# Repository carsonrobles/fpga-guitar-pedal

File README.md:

# FPGA Multi-Effect Guitar Pedal
Carson Robles

## Project Description
This project strives to implement a multi-effect guitar pedal using an FPGA for all of the signal processing.

### Status
In development.

### Goal
The goal of this project is to take the place of multiple separate traditional guitar pedals each with its own dedicated effect.

## Effects
Below is a list of the currently working effects followed by a list of effects that are in development or are planned for future development.

### Working Effects
- Delay
- Distortion (variable gain hard clipping)
- Flanger
- Tremolo

### Effects in Development or Planned for the Future
- Wah Wah
- Phaser

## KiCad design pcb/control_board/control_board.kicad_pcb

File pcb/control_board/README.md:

# FPGA Multi-Effect Guitar Pedal
Carson Robles

## Control Board
The main function of this board is to hold all components of the project including: the FPGA board, the data converter module, control knobs, foot switches, and enable LEDs.

### Status
In fabrication.

## Board Images
### Power System Schematic

Schematic of the power supply that the system runs on. The board accepts 12V in through the onboard barrel jack and produces a regulated 5V supply to power the entire system.

### Effect Enables and Settings Schematic

Schematic of the effect enables and settings potentiometers. These include the 5 foot switches used to enable and disable individual effects. Each effect also includes 2 potentiometer knobs that allow the user to modify each effect to their liking.

### FPGA Board Connections and Analog Mux Schematic

The FPGA is mounted onto the control board via 2 24 pin headers. The analog mux allows only one potentiometer voltage to pass at a time that the FPGA can read using its onboard ADC. The FPGA cycles through which potentiometer value it reads and updates its saved values when a new value is read. The output of the analog mux is filtered and divided down to the range that the onboard ADC can handle, 3.3V.

### Data Converter Module Connections

The data converter module is also mounted to the control board via a Digilent PMOD header (2x6 pin header). This header is routed to I/O pins on the FPGA.

### Front of Board Layout

### Back of Board Layout

### Front of Board Rendering

### Back of Board Rendering

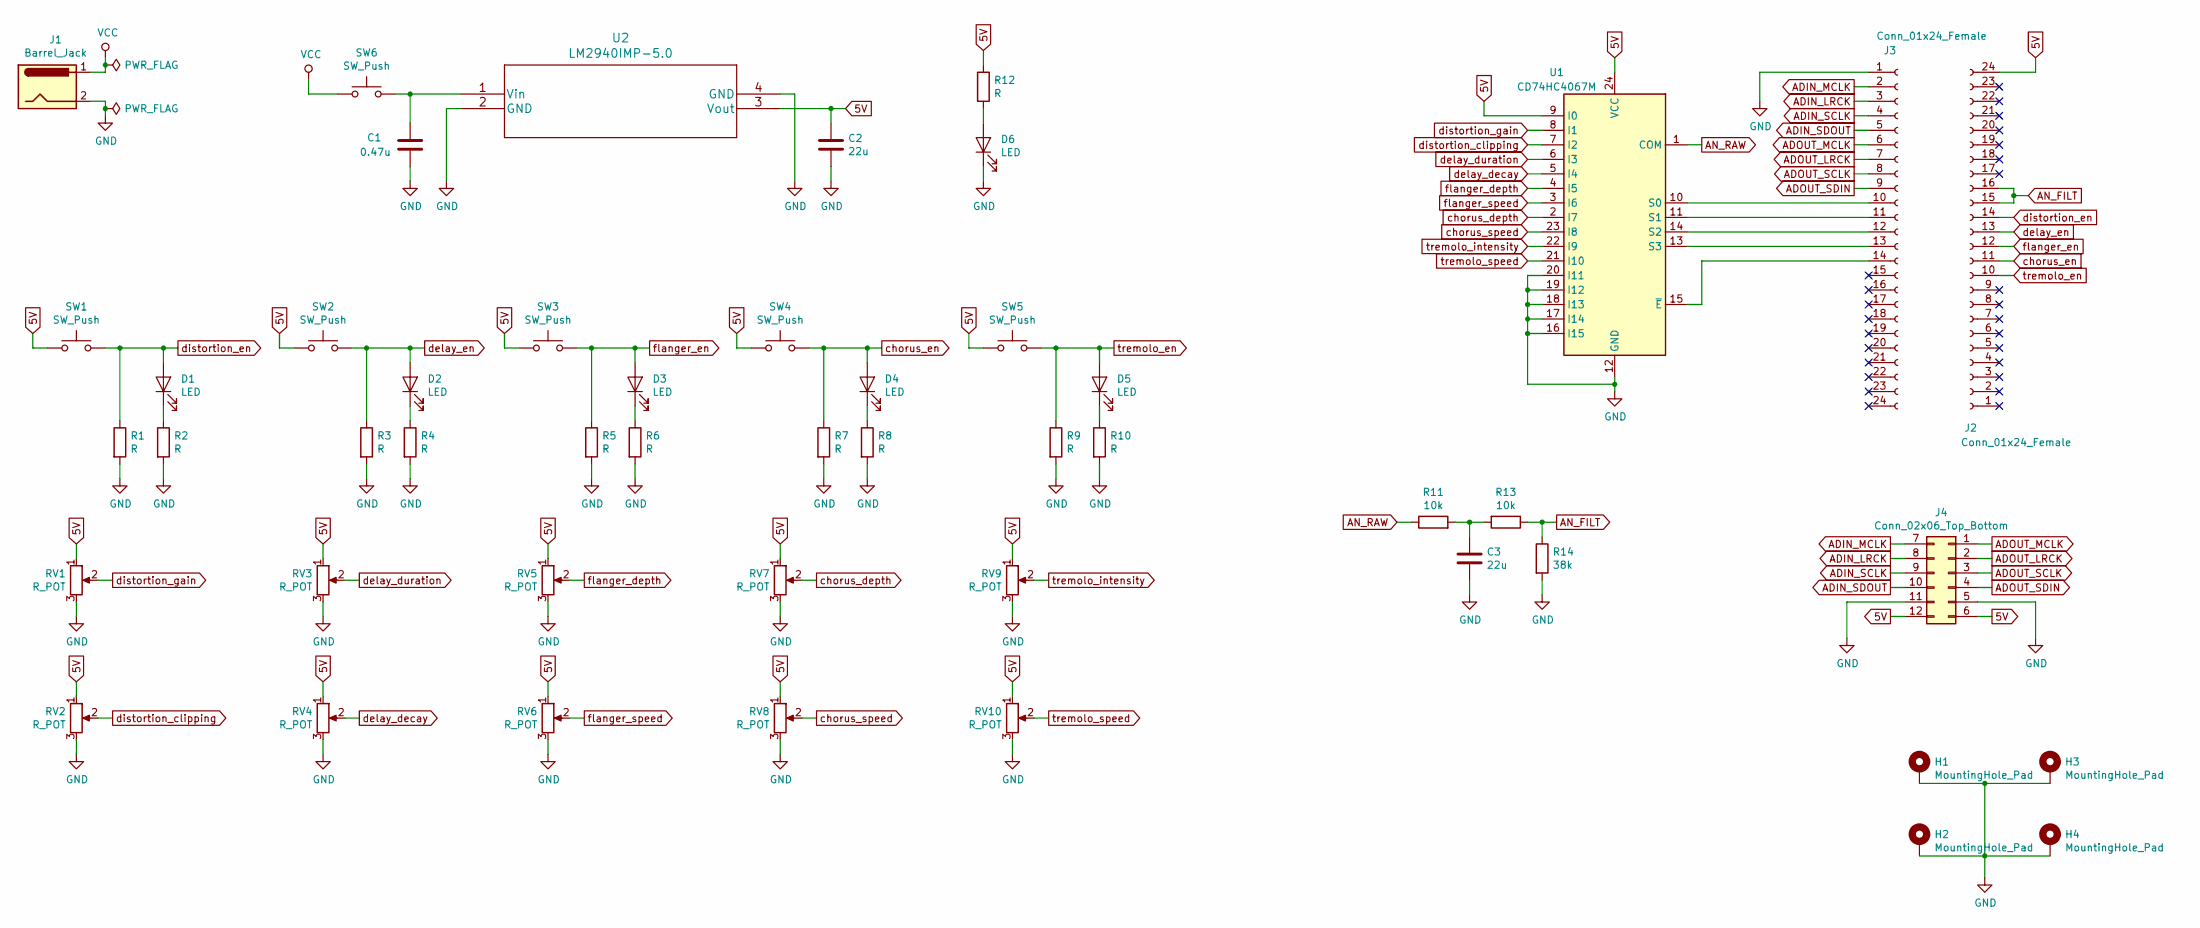
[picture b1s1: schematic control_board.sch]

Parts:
C1: 0.47u; C_0805_2012Metric_Pad1.15x1.40mm_HandSolder
C2, C3: 22u; C_0805_2012Metric_Pad1.15x1.40mm_HandSolder
D1, D2, D3, D4, D5, D6: LED; LED_D4.0mm
H1, H2, H3, H4: MountingHole_Pad; MountingHole_2.5mm_Pad
J1: Barrel_Jack; BarrelJack_CUI_PJ-102AH_Horizontal
J2, J3: Conn_01x24_Female; PinSocket_1x24_P2.54mm_Vertical
J4: Conn_02x06_Top_Bottom; PinHeader_2x06_P2.54mm_Vertical
R1, R2, R3, R4, R5, R6, R7, R8, R9, R10, R12: R; R_0805_2012Metric_Pad1.15x1.40mm_HandSolder
R11, R13: 10k; R_0805_2012Metric_Pad1.15x1.40mm_HandSolder
R14: 38k; R_0805_2012Metric_Pad1.15x1.40mm_HandSolder
RV1, RV2, RV3, RV4, RV5, RV6, RV7, RV8, RV9, RV10: R_POT; Potentiometer_Omeg_PC16BU_Vertical
SW1, SW2, SW3, SW4, SW5, SW6: SW_Push; PinHeader_2x01_P2.54mm_Vertical
U1: CD74HC4067M; SOIC-24W_7.5x15.4mm_P1.27mm
U2: LM2940IMP-5.0

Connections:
5V: C2.1, J2.24, J4.6, J4.12, R12.1, RV1.1, RV2.1, RV3.1, RV4.1, RV5.1, RV6.1, RV7.1, RV8.1, RV9.1, RV10.1, SW1.1, SW2.1, SW3.1, SW4.1, SW5.1, U1.9 (I0), U1.24 (VCC), U2.3 (Vout)
ADIN_LRCK: J3.3, J4.8
ADIN_MCLK: J3.2, J4.7
ADIN_SCLK: J3.4, J4.9
ADIN_SDOUT: J3.5, J4.10
ADOUT_LRCK: J3.7, J4.2
ADOUT_MCLK: J3.6, J4.1
ADOUT_SCLK: J3.8, J4.3
ADOUT_SDIN: J3.9, J4.4
AN_FILT: J2.15, J2.16, R13.1, R14.1
AN_RAW: R11.1, U1.1 (COM)
GND: C1.2, C2.2, C3.2, D6.1 (K), H1.1, H2.1, H3.1, H4.1, J1.2, J3.1, J4.5, J4.11, R1.2, R2.2, R3.2, R4.2, R5.2, R6.2, R7.2, R8.2, R9.2, R10.2, R14.2, RV1.3, RV2.3, RV3.3, RV4.3, RV5.3, RV6.3, RV7.3, RV8.3, RV9.3, RV10.3, U1.12 (GND), U1.16 (I15), U1.17 (I14), U1.18 (I13), U1.19 (I12), U1.20 (I11), U2.2 (GND), U2.4 (GND)
unnamed: C1.1, SW6.2, U2.1 (Vin)
unnamed: C3.1, R11.2, R13.2
unnamed: D1.1 (K), R2.1
unnamed: D2.1 (K), R4.1
unnamed: D3.1 (K), R6.1
unnamed: D4.1 (K), R8.1
unnamed: D5.1 (K), R10.1
unnamed: D6.2 (A), R12.2
unnamed: J3.10, U1.10 (S0)
unnamed: J3.11, U1.11 (S1)
unnamed: J3.12, U1.14 (S2)
unnamed: J3.13, U1.13 (S3)
unnamed: J3.14, U1.15 (~E)
VCC: J1.1, SW6.1
chorus_depth: RV7.2, U1.2 (I7)
chorus_en: D4.2 (A), J2.11, R7.1, SW4.2
chorus_speed: RV8.2, U1.23 (I8)
delay_decay: RV4.2, U1.5 (I4)
delay_duration: RV3.2, U1.6 (I3)
delay_en: D2.2 (A), J2.13, R3.1, SW2.2
distortion_clipping: RV2.2, U1.7 (I2)
distortion_en: D1.2 (A), J2.14, R1.1, SW1.2
distortion_gain: RV1.2, U1.8 (I1)
flanger_depth: RV5.2, U1.4 (I5)
flanger_en: D3.2 (A), J2.12, R5.1, SW3.2
flanger_speed: RV6.2, U1.3 (I6)
tremolo_en: D5.2 (A), J2.10, R9.1, SW5.2
tremolo_intensity: RV9.2, U1.22 (I9)
tremolo_speed: RV10.2, U1.21 (I10)

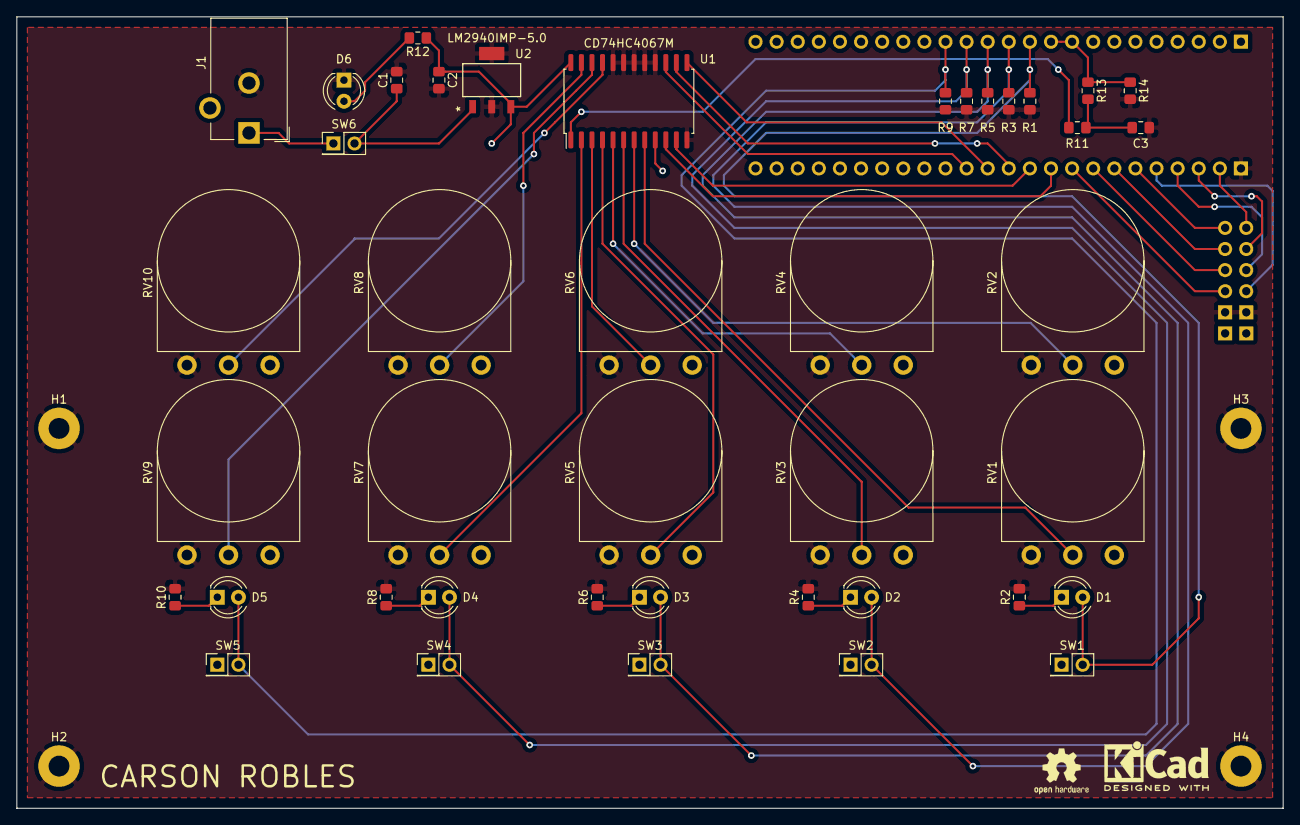
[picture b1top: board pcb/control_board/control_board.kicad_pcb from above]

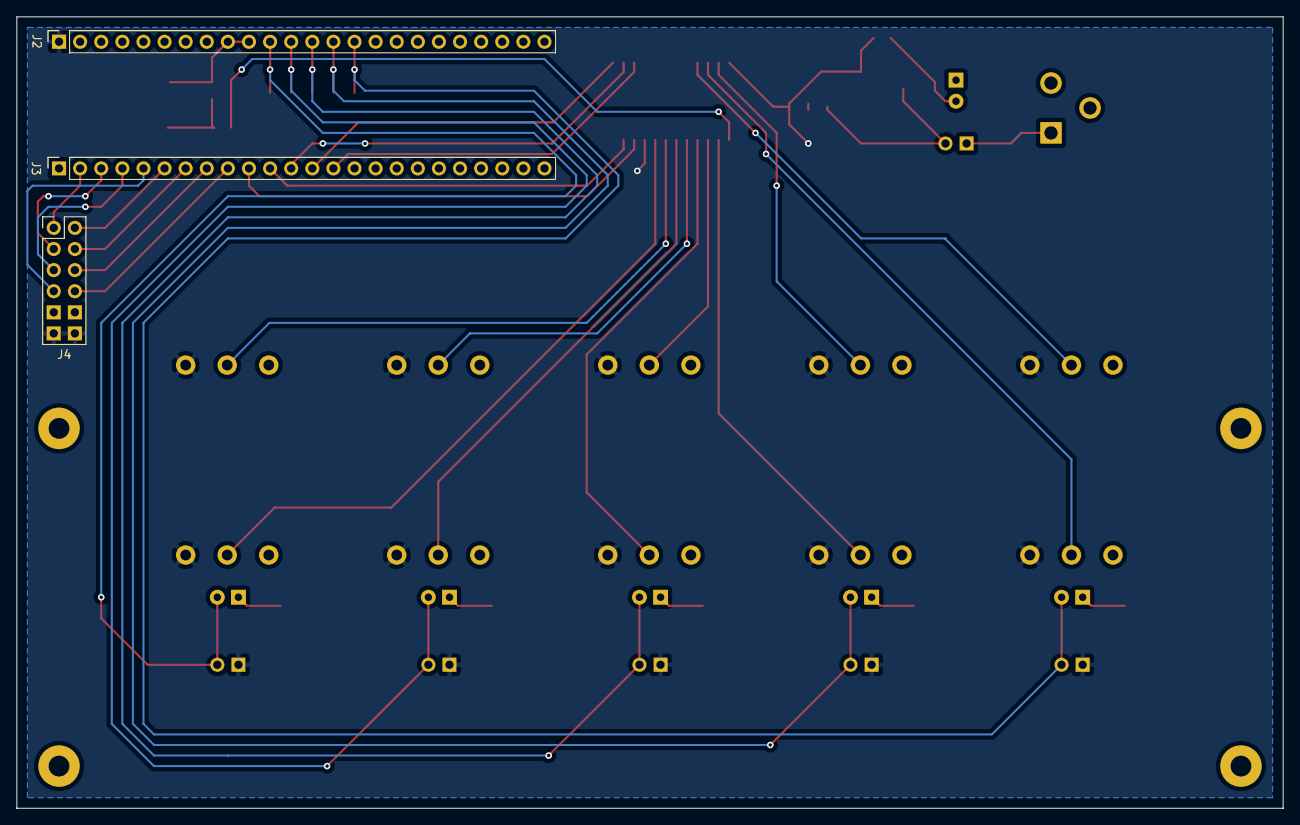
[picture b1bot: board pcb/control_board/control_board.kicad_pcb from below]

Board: 2 copper layers, 152.4 x 95.2 mm, 49 parts (3 on the bottom side), 41 nets.

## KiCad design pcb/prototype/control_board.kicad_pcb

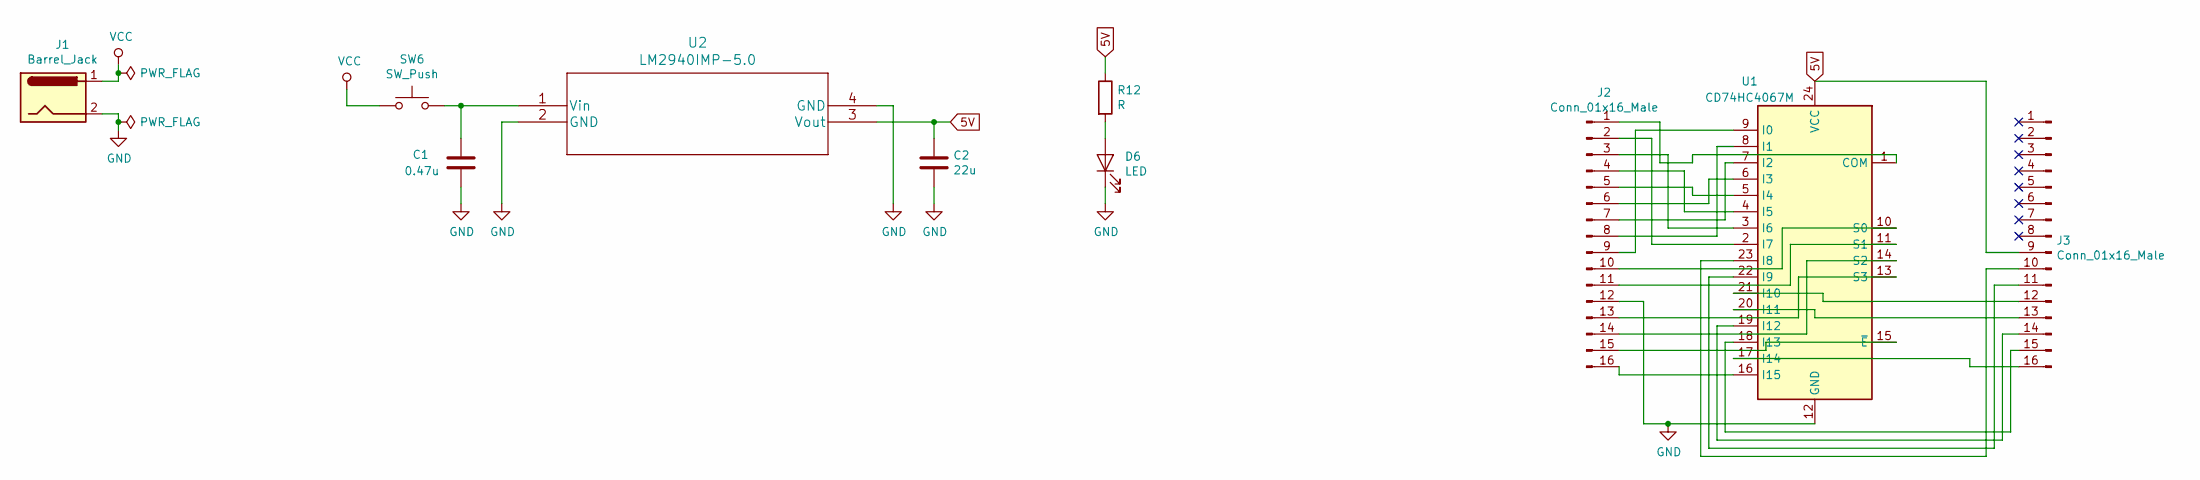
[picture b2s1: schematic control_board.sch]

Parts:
C1: 0.47u; C_0805_2012Metric_Pad1.15x1.40mm_HandSolder
C2: 22u; C_0805_2012Metric_Pad1.15x1.40mm_HandSolder
D6: LED; LED_D4.0mm
J1: Barrel_Jack; BarrelJack_CUI_PJ-102AH_Horizontal
J2, J3: Conn_01x16_Male; PinHeader_1x16_P2.54mm_Vertical
R12: R; R_Axial_DIN0309_L9.0mm_D3.2mm_P12.70mm_Horizontal
SW6: SW_Push; SolderWirePad_1x02_P7.62mm_Drill2.5mm
U1: CD74HC4067M; SOIC-24W_7.5x15.4mm_P1.27mm
U2: LM2940IMP-5.0

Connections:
5V: C2.1, J3.9, R12.1, U1.24 (VCC), U2.3 (Vout)
GND: C1.2, C2.2, D6.1 (K), J1.2, J2.12, U1.12 (GND), U2.2 (GND), U2.4 (GND)
unnamed: C1.1, SW6.2, U2.1 (Vin)
unnamed: D6.2 (A), R12.2
unnamed: J2.1, U1.1 (COM)
unnamed: J2.2, U1.2 (I7)
unnamed: J2.3, U1.3 (I6)
unnamed: J2.4, U1.4 (I5)
unnamed: J2.5, U1.5 (I4)
unnamed: J2.6, U1.6 (I3)
unnamed: J2.7, U1.7 (I2)
unnamed: J2.8, U1.8 (I1)
unnamed: J2.9, U1.9 (I0)
unnamed: J2.10, U1.10 (S0)
unnamed: J2.11, U1.11 (S1)
unnamed: J2.13, U1.13 (S3)
unnamed: J2.14, U1.14 (S2)
unnamed: J2.15, U1.15 (~E)
unnamed: J2.16, U1.16 (I15)
unnamed: J3.10, U1.23 (I8)
unnamed: J3.11, U1.22 (I9)
unnamed: J3.12, U1.21 (I10)
unnamed: J3.13, U1.20 (I11)
unnamed: J3.14, U1.19 (I12)
unnamed: J3.15, U1.18 (I13)
unnamed: J3.16, U1.17 (I14)
VCC: J1.1, SW6.1

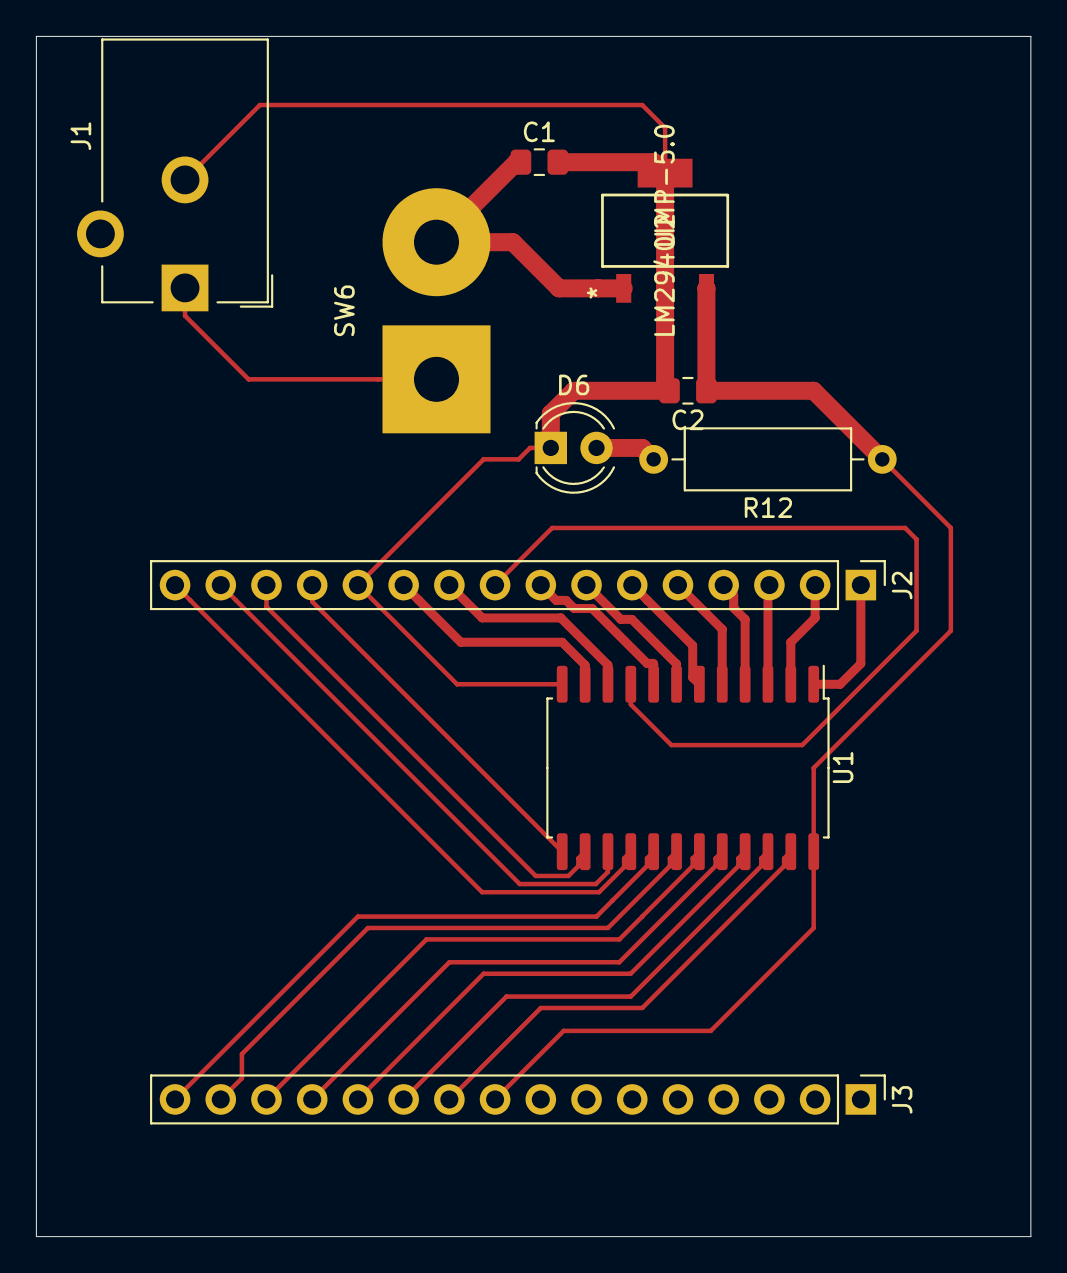
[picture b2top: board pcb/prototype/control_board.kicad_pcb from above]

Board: 2 copper layers, 55.2 x 66.7 mm, 10 parts (0 on the bottom side), 27 nets.

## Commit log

2019-01-24 Add initial python simulations. Start I2S interface.
2019-01-28 Add scripted build and constraints file to project. Implement I2S clock generation.
2019-01-29 Pass through working, needs cleanup.
2019-01-29 Move rgb simulation sources to sim folder. Clean up i2s_rx and i2s_tx.
2019-01-29 Fix Makefile and syncth.tcl so that scripted build works with PLL IP.
2019-01-29 Move sinusoid function from main.py to audio.py.
2019-02-01 Remove AXI handshake interface and replace with just a valid flag. This should be just fine since there should never be a situation where there is back pressure because this would imply the sampling 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
2019-02-01 Add blank effects pipe.
2019-02-03 Combine I2S modules into one and generate the clocks internally rather than with an additional module.
2019-02-03 Modify effects pipe to use only left channel of full audio sample.
2019-02-08 Finish hard clipping effect.
2019-02-13 Add tremolo python sim. Begin triangle wave generator.
2019-02-14 Add working constant delay effect.
2019-02-15 Update README to have more information on the project and its status.
2019-02-17 Rename delay fifo.
2019-02-17 Add initial tremolo effect.
2019-02-19 Update Makefile to have program target and program tcl script to program board.
2019-02-19 Test tremolo, delay, and hard clipping.
2019-02-26 Remove unused include in eff_hard_clip.
2019-02-26 Add python tool to generate sine wave look up table.
2019-02-26 Add initial working version of the NCO.
2019-02-28 Move triangle wave generate to nco folder.
2019-02-28 Add flag to routing script for complete timing analysis.
2019-02-28 Change RGB module reset to reset button rather than synchronized reset (to mclk) to avoid failed timing.
2019-02-28 Add python tool to print warnings and error from all stages of compilation after a complete build.
2019-02-28 Update README.
2019-03-01 Add generic FIR module.
2019-03-25 Add wah effect. Effect still has some slight noise that needs to be fixed.
2019-04-25 Fix periodic noise in flanger effect. Need code clean up before pushing to master.
2019-04-25 Clean up flanger code.
2019-05-13 First revision of control board complete.
2019-05-13 Remove unused protoype directory.
2019-05-14 Port project to CMOD A7 board.
2019-05-15 Correctly place CMOD headers, add divider to filter to drop potentiometer voltage into range of CMOD ADC.
2019-05-15 Add connectors for switches rather than holes for direct wires.
2019-05-16 Final board changes.
2019-05-16 Update gitignore remove old effects schematics.
2019-05-16 Add README to control board directory.

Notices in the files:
parts and their libraries:
Copyright 2016 Accelerated Designs. All rights reserved.
